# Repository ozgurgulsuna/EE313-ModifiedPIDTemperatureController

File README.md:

<h3 align="center" style=" border-bottom: none ;">EE313 Term Project </h3>
<p align="center">
   
<h2 align="center" style=" border-bottom: none ;">Design of an Autonomous Temperature Conditioning System Using Modified Analog PID Controller</h2>
<p align="center">

<h3 align="center" style=" border-bottom: none ;"> Project Summary </h3>
<p align="center">

<p align="justify">
&nbsp&nbsp Air conditioning can be described as the process of cooling, heating, moisturizing, dehumidifying, etc.
This method is utilized to create a more pleasant interior environment. In this project, you are required
to design an air conditioner system for small spaces. The system acquires heating, and cooling functions
and consists of one variable set input and four subsystems, namely, the control unit, display unit, sensing
unit, and the operation unit. The sensing unit provides the ambient temperature to the control unit, and
the temperature adjustment unit provides the desired temperature to the control unit. Figure 1 shows
the block diagram of the system.
</p>

<p align="center">
 </a>
</p>

<p align="justify">
&nbsp&nbsp Thus to design a responsive, fast, and accurate temperature control system PID method is a feasible choice. One challenge, of applying PID method to this problem is that the heating and cooling processes are not symmetric. To compensate that, a modified PID control circuit will be introduced in this paper. Also, to avoid the EMI (Electromagnetic Interference) and noise problems, the circuit is designed on a PCB (Printed Circuit Board). The heating element is a nickel-chromium wire and the cooling element is an 12V DC fan. The fan and the heater are driven with a MOSFET switch which is controlled by the generated PWM (Pulse Width Modulation) signals. The PWM for each switch is generated by comparing a triangular wave with the PID outputs.
</p>
   
<p align="justify">
&nbsp&nbsp The ambient temperature is measured using the LM35 analog temperature sensor. The set temperature value is adjusted with a potentiometer. The set and ambient temperatures are displayed by the display unit which consist of RGB LEDs (Red Green Blue Light Emitting Diodes), a constant current LED drive utilized by a transconductance amplifier. The display unit designed in a way to emit red light at 24°Cand below, green light at 32°Cand blue light at 40°C and above. The display output for the temperature intervals between those values are produced by combining the colors in a way that a smooth transition is observed while the set and ambient temperatures are changed.
</p>

<p align="justify">
&nbsp&nbsp In this project, first the design methodology and the mathematical analysis of each unit will be discussed in detail in section II. The circuit schematics and their analysis will be given in this part. The mechanical design and the manufacturing will be discussed in section III. Then, thermal modelling of the system will be explained in section IV. The results of the performed LTspice simulations will be given in section V. The experimental results and the comparison with the simulation will follow in section VI. Finally, the conclusions will be drawn in section VII.
</p>

<h3 align="center" style=" border-bottom: none ;"> Report </h3>
<p align="center">
   
<p align="justify">
&nbsp&nbsp In this <a href="https://github.com/ozgurgulsuna/EE313-ModifiedPIDTemperatureController/blob/main/Design%20of%20an%20Autonomous%20Temperature%20Conditioning%20System%20Using%20Modified%20PID%20Controller.pdf">report </a>, the design and implementation of an autonomous temperature conditioning system is demonstrated. Electrical and thermal systems are modelled in a single simulation environment with feedback loop closed. The PID method is shown that its applicable to this system, but due to the asymmetry of the reverse processes a modified PID circuit is proposed to damp oscillations of the system around the steady state, which is shown to be successful with the experimental results. Moreover, since the control signals are critical for the process, it is observed that filtering the noise with low and high pass filters and also avoiding the EMI effects with a careful PCB design procedure is essential for an accurate and reliable control mechanism.
</p>

<p align="center">
   </a>
</p>

<h3 align="center" style=" border-bottom: none ;"> Photographs </h3>

<p align="center">
   
<p align="center">
    
    &nbsp&nbsp 
    
</p>

<p align="center">
    
    &nbsp&nbsp 
    
</p>

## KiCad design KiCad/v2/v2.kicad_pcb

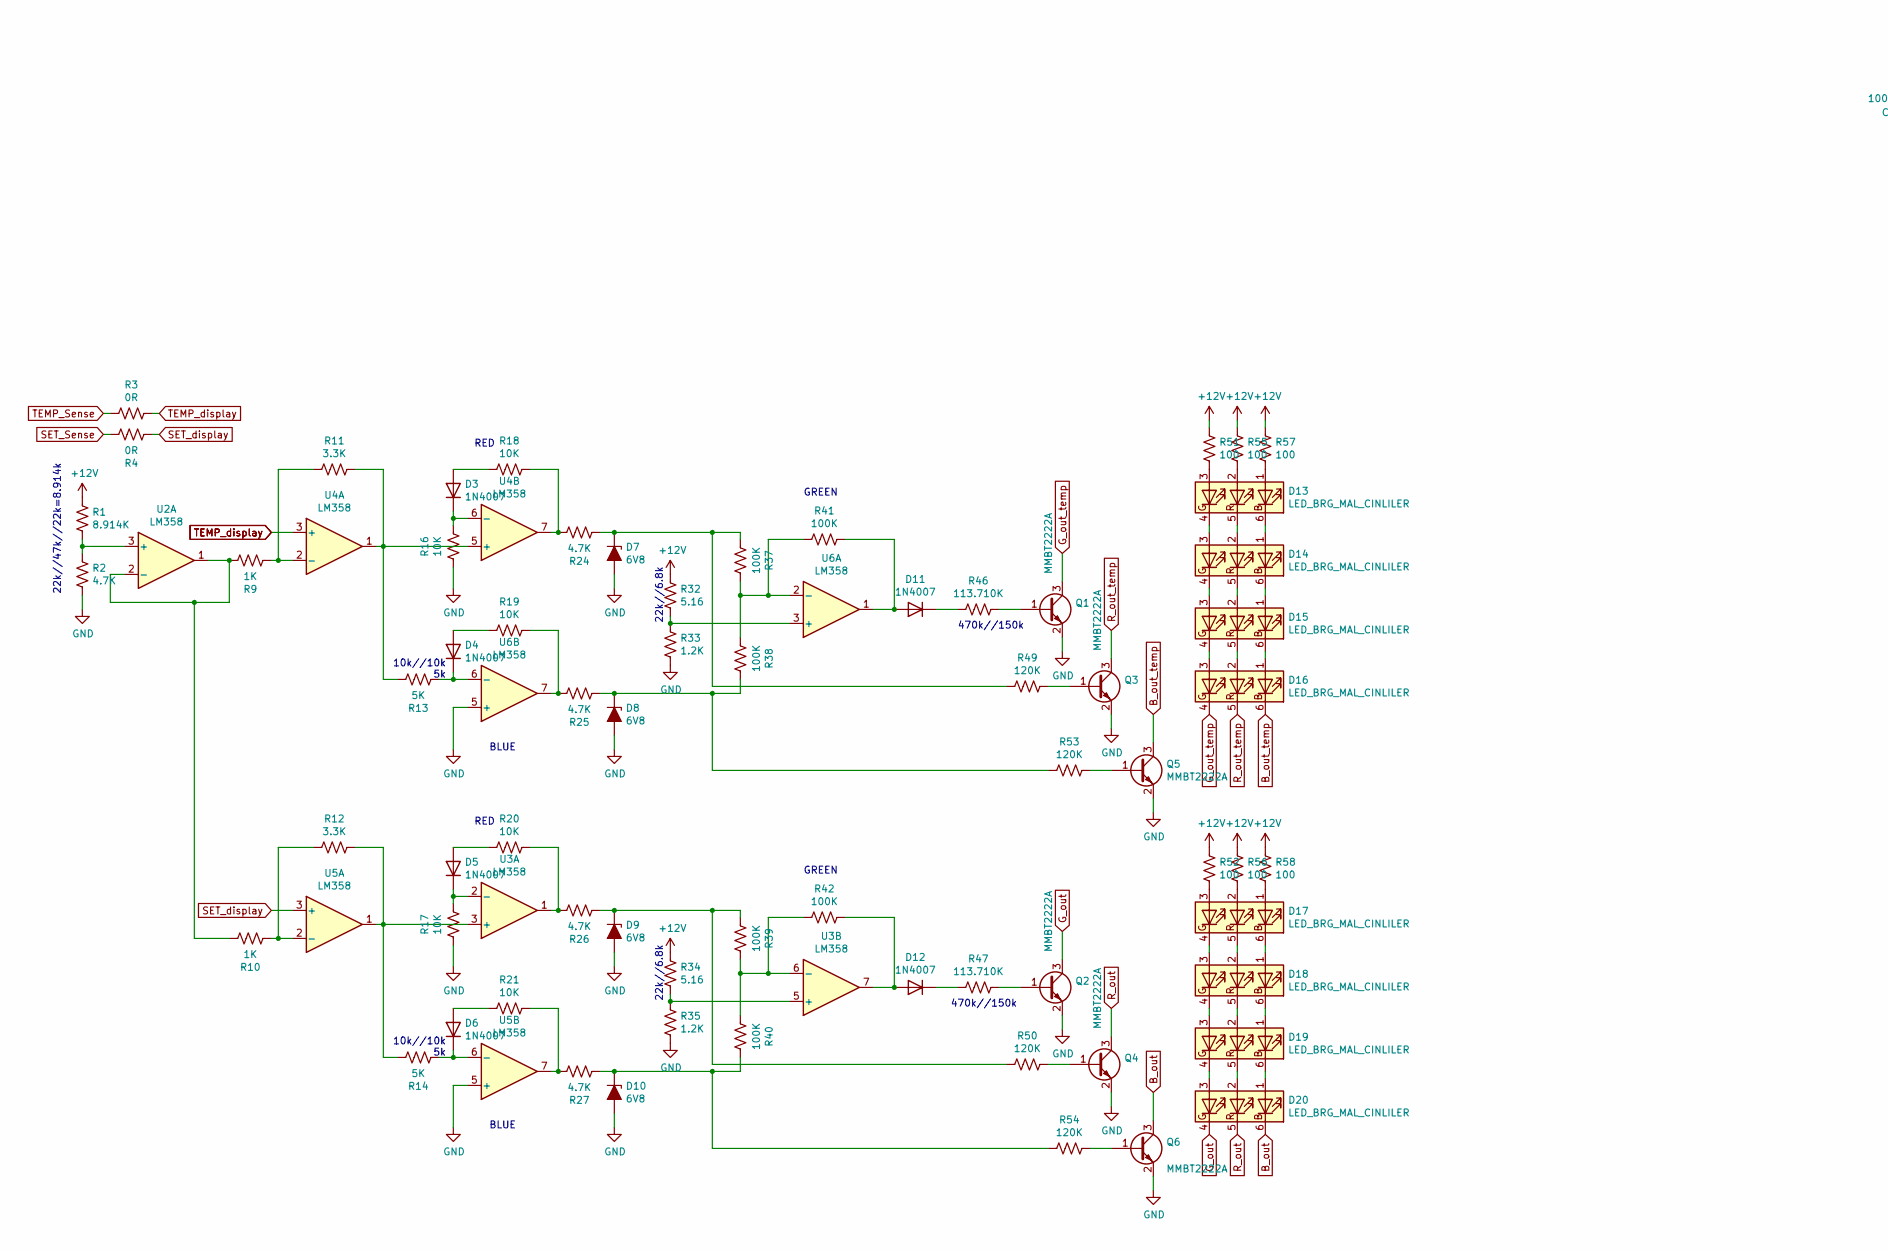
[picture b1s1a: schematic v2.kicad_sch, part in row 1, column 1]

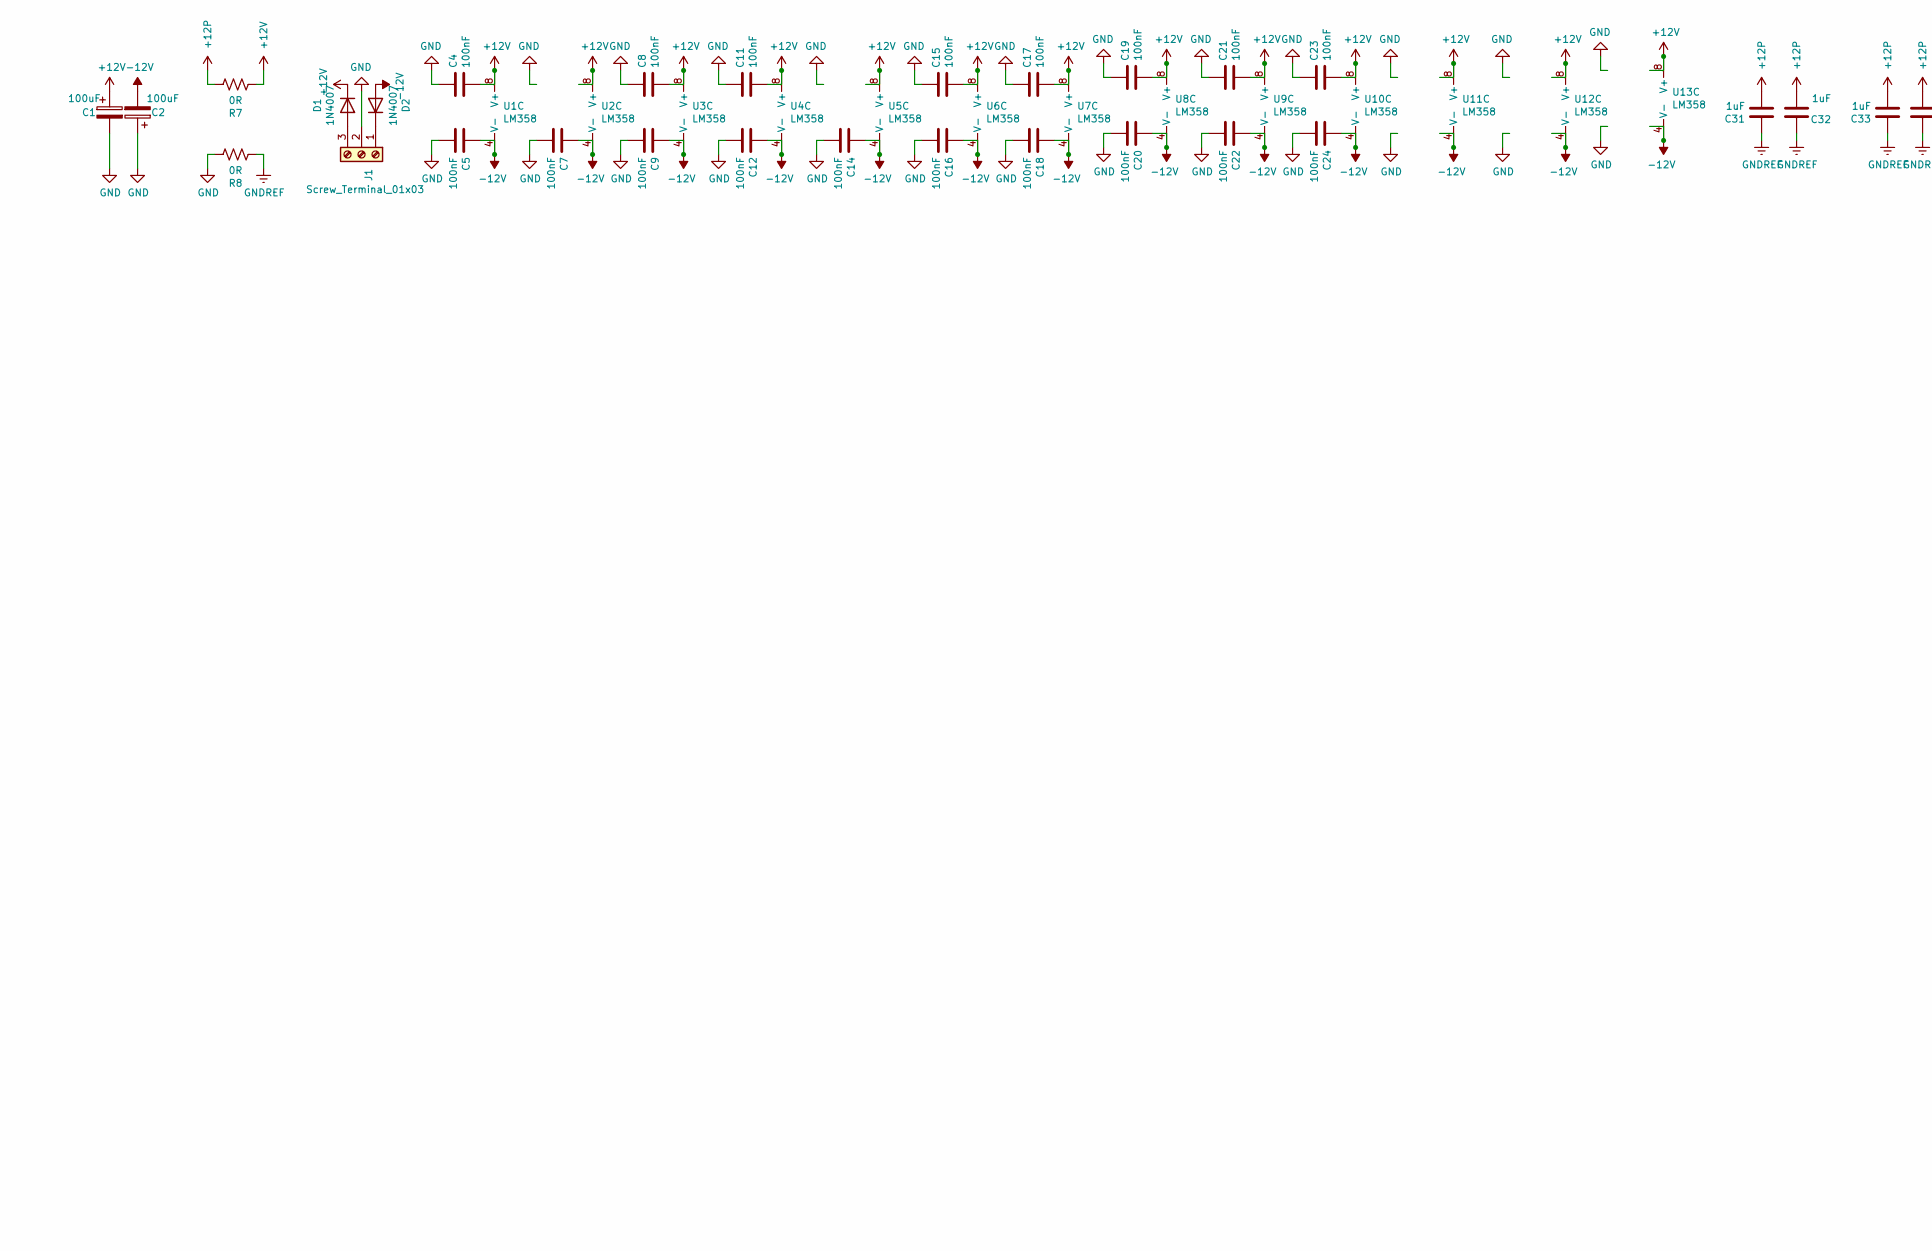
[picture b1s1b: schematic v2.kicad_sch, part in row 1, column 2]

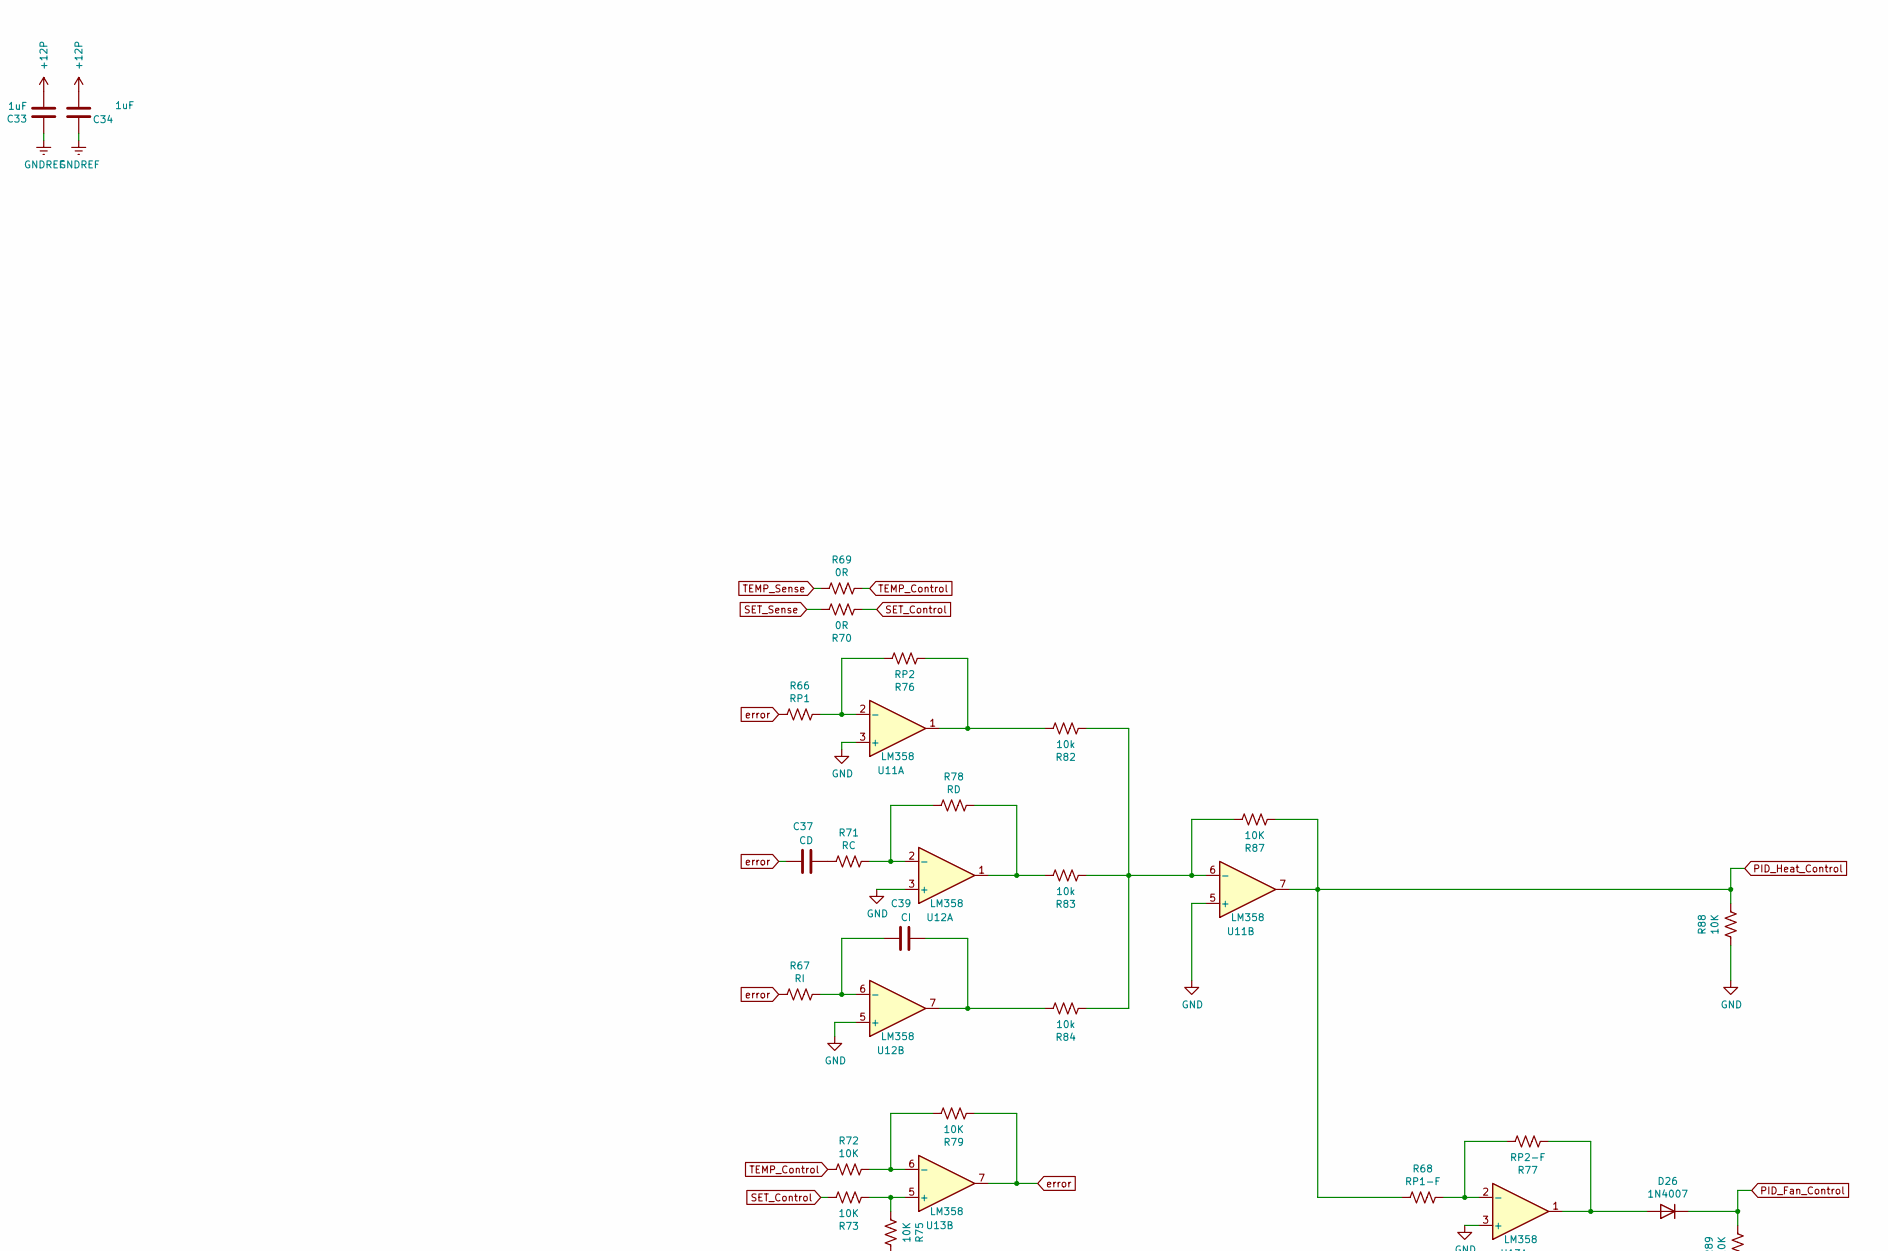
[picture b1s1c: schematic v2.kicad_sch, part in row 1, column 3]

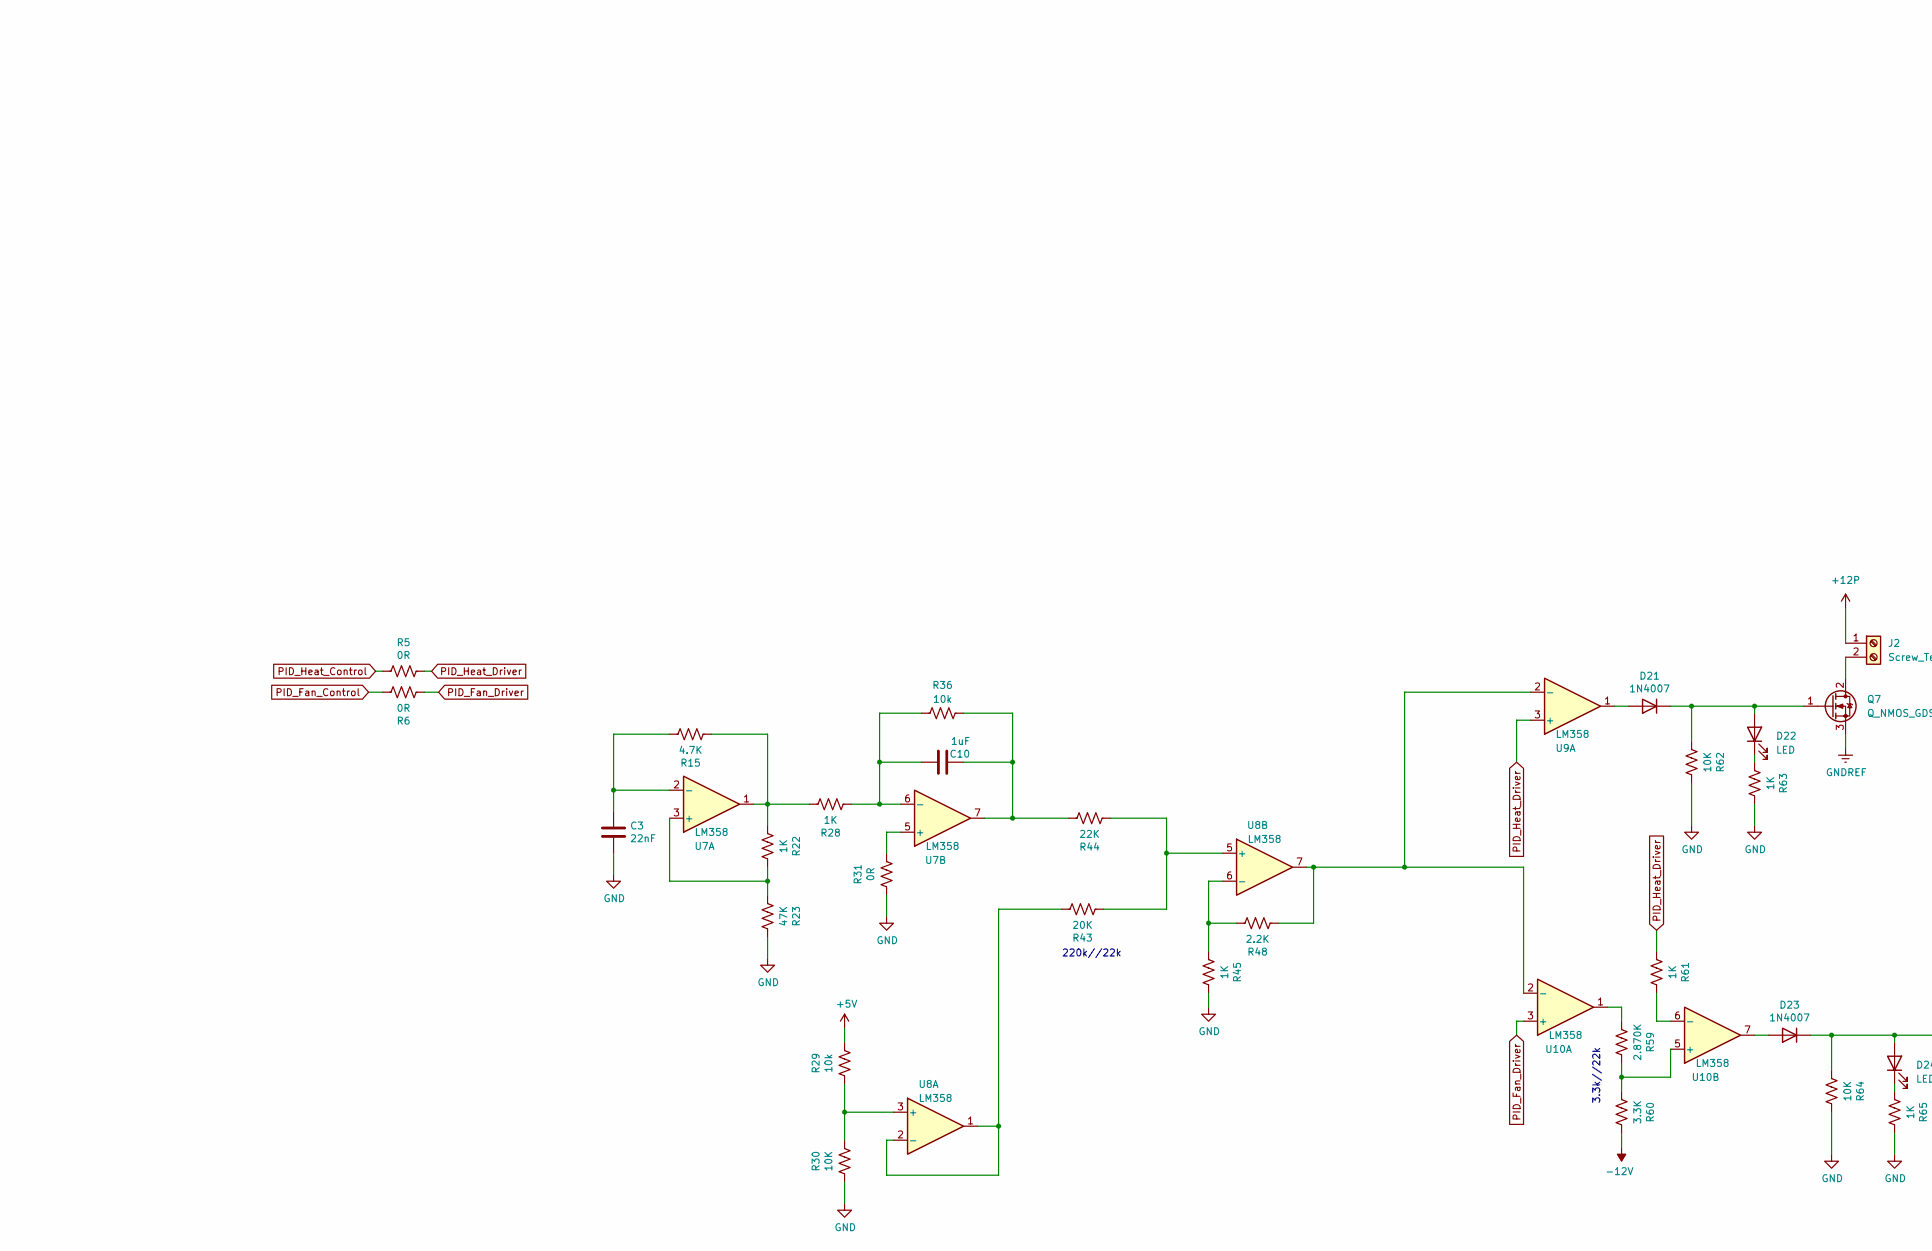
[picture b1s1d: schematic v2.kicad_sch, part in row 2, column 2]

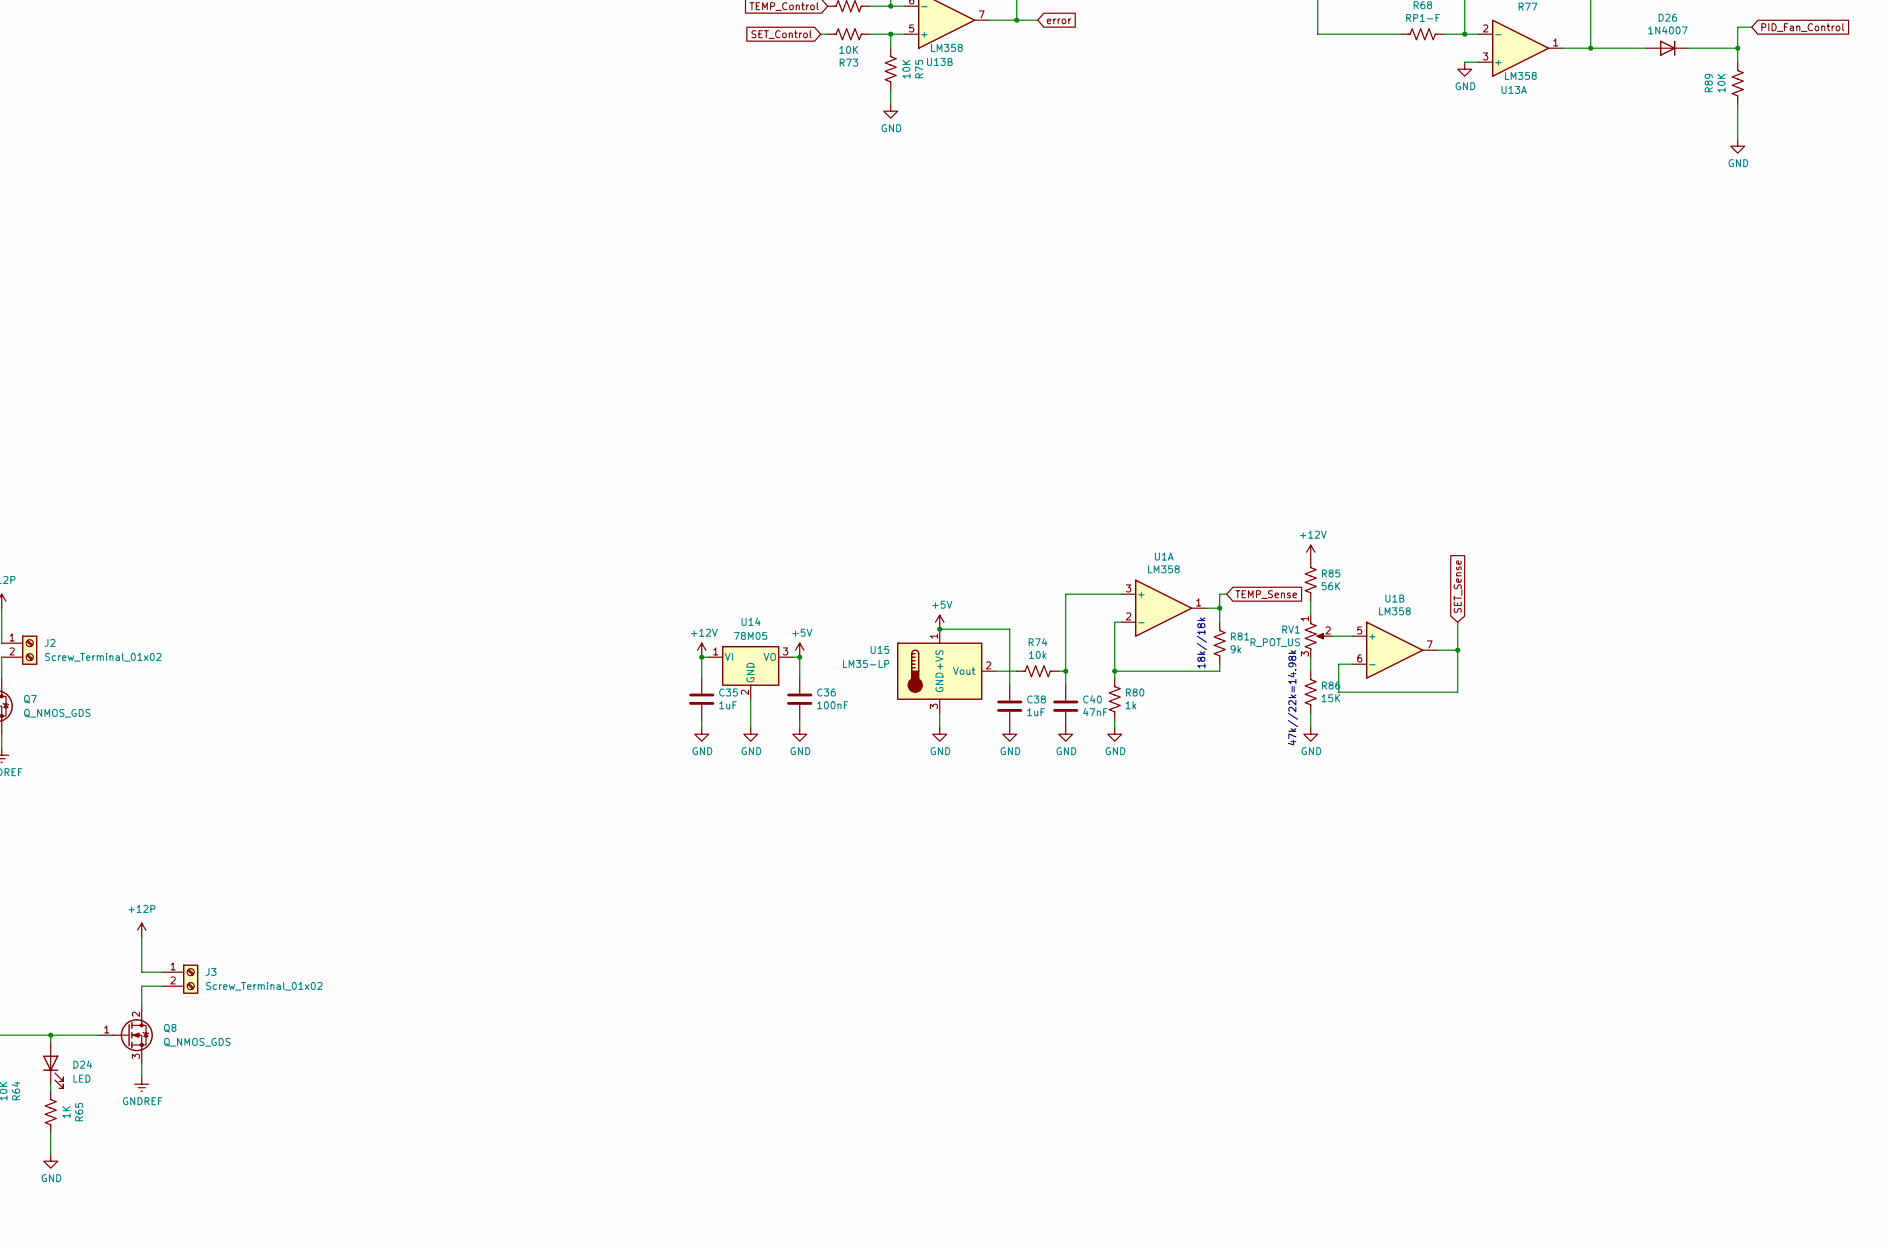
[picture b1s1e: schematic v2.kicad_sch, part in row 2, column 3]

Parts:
C1, C2: 100uF; CP_Elec_6.3x5.7
C3: 22nF; R_1206_3216Metric_Pad1.30x1.75mm_HandSolder
C4, C5, C7, C8, C9, C11, C12, C14, C15, C16, C17, C18, C19, C20, C21, C22, C23, C24, C36: 100nF; R_1206_3216Metric_Pad1.30x1.75mm_HandSolder
C10, C31, C32, C33, C34, C35, C38: 1uF; R_1206_3216Metric_Pad1.30x1.75mm_HandSolder
C37: CD; R_1206_3216Metric_Pad1.30x1.75mm_HandSolder
C39: CI; R_1206_3216Metric_Pad1.30x1.75mm_HandSolder
C40: 47nF; R_0805_2012Metric_Pad1.20x1.40mm_HandSolder
D1, D2, D3, D4, D5, D6, D11, D12, D21, D23, D26: 1N4007; D_SMA_Handsoldering
D7, D8, D9, D10: 6V8; D_A-405_P5.08mm_Vertical_KathodeUp
D13, D14, D15, D16, D17, D18, D19, D20: LED_BRG_MAL_CINLILER; LED_RGB_5050-6
D22, D24: LED; R_1206_3216Metric_Pad1.30x1.75mm_HandSolder
J1: Screw_Terminal_01x03; DEGSONx3x3.81mm
J2, J3: Screw_Terminal_01x02; R_Axial_DIN0204_L3.6mm_D1.6mm_P1.90mm_Vertical
Q1, Q2, Q3, Q4, Q5, Q6: MMBT2222A
Q7, Q8: Q_NMOS_GDS; TO-252-2
R1: 8.914K; R_1206_3216Metric_Pad1.30x1.75mm_HandSolder
R2, R15, R24, R25, R26, R27: 4.7K; R_1206_3216Metric_Pad1.30x1.75mm_HandSolder
R3, R4, R5, R6, R7, R8, R31, R69, R70: 0R; R_1206_3216Metric_Pad1.30x1.75mm_HandSolder
R9, R10, R22, R28, R45, R61, R63, R65: 1K; R_1206_3216Metric_Pad1.30x1.75mm_HandSolder
R11, R12, R60: 3.3K; R_1206_3216Metric_Pad1.30x1.75mm_HandSolder
R13, R14: 5K; R_1206_3216Metric_Pad1.30x1.75mm_HandSolder
R16, R17, R18, R19, R20, R21, R30, R62, R64, R72, R73, R75, R79, R87, R88, R89: 10K; R_1206_3216Metric_Pad1.30x1.75mm_HandSolder
R23: 47K; R_1206_3216Metric_Pad1.30x1.75mm_HandSolder
R29, R36, R74, R82, R83, R84: 10k; R_1206_3216Metric_Pad1.30x1.75mm_HandSolder
R32, R34: 5.16; R_1206_3216Metric_Pad1.30x1.75mm_HandSolder
R33, R35: 1.2K; R_1206_3216Metric_Pad1.30x1.75mm_HandSolder
R37, R38, R39, R40, R41, R42: 100K; R_1206_3216Metric_Pad1.30x1.75mm_HandSolder
R43: 20K; R_1206_3216Metric_Pad1.30x1.75mm_HandSolder
R44: 22K; R_1206_3216Metric_Pad1.30x1.75mm_HandSolder
R46, R47: 113.710K; R_1206_3216Metric_Pad1.30x1.75mm_HandSolder
R48: 2.2K; R_1206_3216Metric_Pad1.30x1.75mm_HandSolder
R49, R50, R53, R54: 120K; R_1206_3216Metric_Pad1.30x1.75mm_HandSolder
R51, R52, R55, R56, R57, R58: 100; R_1206_3216Metric_Pad1.30x1.75mm_HandSolder
R59: 2.870K; R_1206_3216Metric_Pad1.30x1.75mm_HandSolder
R66: RP1; R_1206_3216Metric_Pad1.30x1.75mm_HandSolder
R67: RI; R_1206_3216Metric_Pad1.30x1.75mm_HandSolder
R68: RP1-F; R_1206_3216Metric_Pad1.30x1.75mm_HandSolder
R71: RC; R_1206_3216Metric_Pad1.30x1.75mm_HandSolder
R76: RP2; R_1206_3216Metric_Pad1.30x1.75mm_HandSolder
R77: RP2-F; R_1206_3216Metric_Pad1.30x1.75mm_HandSolder
R78: RD; R_1206_3216Metric_Pad1.30x1.75mm_HandSolder
R80: 1k; R_1206_3216Metric_Pad1.30x1.75mm_HandSolder
R81: 9k; R_1206_3216Metric_Pad1.30x1.75mm_HandSolder
R85: 56K; R_1206_3216Metric_Pad1.30x1.75mm_HandSolder
R86: 15K; R_1206_3216Metric_Pad1.30x1.75mm_HandSolder
RV1: R_POT_US; 20kpot
U1, U2, U3, U4, U5, U6, U7, U8, U9, U10, U11, U12, U13: LM358; SOIC-8_3.9x4.9mm_P1.27mm
U14: 78M05; TO-252-2
U15: LM35-LP; TO-92

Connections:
+5V: C36.1, C38.1, R29.2, U14.3 (VO), U15.1 (+VS); also elsewhere on the board
+12P: C31.2, C32.2, C33.2, C34.2, J2.1, J3.1, R7.2
+12V: C1.1, C4.2, C8.2, C11.2, C15.2, C17.2, C19.2, C21.2, C23.2, C35.1, D1.1 (K), R1.2, R7.1, R32.2, R34.2, R51.1, R52.1, R55.1, R56.1, R57.1, R58.1, R85.2, U1.8 (V+), U2.8 (V+), U3.8 (V+), U4.8 (V+), U5.8 (V+), U6.8 (V+), U7.8 (V+), U8.8 (V+), U9.8 (V+), U10.8 (V+), U11.8 (V+), U12.8 (V+), U13.8 (V+), U14.1 (VI)
-12V: C2.2, C5.1, C7.1, C9.1, C12.1, C14.1, C16.1, C18.1, C20.1, C22.1, C24.1, D2.2 (A), R60.2, U1.4 (V-), U2.4 (V-), U3.4 (V-), U4.4 (V-), U5.4 (V-), U6.4 (V-), U7.4 (V-), U8.4 (V-), U9.4 (V-), U10.4 (V-), U11.4 (V-), U12.4 (V-), U13.4 (V-)
B_out: D20.6 (RA), Q6.3 (C)
B_out_temp: D16.6 (RA), Q5.3 (C)
G_out: D20.4 (BA), Q2.3 (C)
G_out_temp: D16.4 (BA), Q1.3 (C)
unnamed: C3.1, R15.2, U7.2 (-)
unnamed: C10.1, R28.1, R36.2, U7.6 (-)
unnamed: C10.2, R36.1, R44.2, U7.7
unnamed: C37.2, R71.1
unnamed: C39.1, R67.2, U12.6 (-)
unnamed: C39.2, R84.2, U12.7
unnamed: C40.1, R74.1, U1.3 (+)
unnamed: D1.2 (A), J1.3
unnamed: D2.1 (K), J1.1
unnamed: D3.1 (K), R16.2, U4.6 (-)
unnamed: D3.2 (A), R18.1
unnamed: D4.1 (K), R13.1, U6.6 (-)
unnamed: D4.2 (A), R19.1
unnamed: D5.1 (K), R17.2, U3.2 (-)
unnamed: D5.2 (A), R20.1
unnamed: D6.1 (K), R14.1, U5.6 (-)
unnamed: D6.2 (A), R21.1
unnamed: D7.1 (K), R24.1, R37.1, R49.1
unnamed: D8.1 (K), R25.1, R38.2, R53.1
unnamed: D9.1 (K), R26.1, R39.1, R50.1
unnamed: D10.1 (K), R27.1, R40.2, R54.1
unnamed: D11.1 (K), R46.1
unnamed: D11.2 (A), R41.2, U6.1
unnamed: D12.1 (K), R47.1
unnamed: D12.2 (A), R42.2, U3.7
unnamed: D13.1 (RK), R57.2
unnamed: D13.2 (GK), R55.2
unnamed: D13.3 (BK), R51.2
unnamed: D13.4 (BA), D14.3 (BK)
unnamed: D13.5 (GA), D14.2 (GK)
unnamed: D13.6 (RA), D14.1 (RK)
unnamed: D14.4 (BA), D15.3 (BK)
unnamed: D14.5 (GA), D15.2 (GK)
unnamed: D14.6 (RA), D15.1 (RK)
unnamed: D15.4 (BA), D16.3 (BK)
unnamed: D15.5 (GA), D16.2 (GK)
unnamed: D15.6 (RA), D16.1 (RK)
unnamed: D17.1 (RK), R58.2
unnamed: D17.2 (GK), R56.2
unnamed: D17.3 (BK), R52.2
unnamed: D17.4 (BA), D18.3 (BK)
unnamed: D17.5 (GA), D18.2 (GK)
unnamed: D17.6 (RA), D18.1 (RK)
unnamed: D18.4 (BA), D19.3 (BK)
unnamed: D18.5 (GA), D19.2 (GK)
unnamed: D18.6 (RA), D19.1 (RK)
unnamed: D19.4 (BA), D20.3 (BK)
unnamed: D19.5 (GA), D20.2 (GK)
unnamed: D19.6 (RA), D20.1 (RK)
unnamed: D21.1 (K), D22.2 (A), Q7.1 (G), R62.1
unnamed: D21.2 (A), U9.1
unnamed: D22.1 (K), R63.1
unnamed: D23.1 (K), D24.2 (A), Q8.1 (G), R64.1
unnamed: D23.2 (A), U10.7
unnamed: D24.1 (K), R65.1
unnamed: D26.2 (A), R77.1, U13.1
unnamed: J2.2, Q7.2 (D)
unnamed: J3.2, Q8.2 (D)
unnamed: Q1.1 (B), R46.2
unnamed: Q2.1 (B), R47.2
unnamed: Q3.1 (B), R49.2
unnamed: Q4.1 (B), R50.2
unnamed: Q5.1 (B), R53.2
unnamed: Q6.1 (B), R54.2
unnamed: R1.1, R2.2, U2.3 (+)
unnamed: R10.1, R12.1, U5.2 (-)
unnamed: R9.2, R10.2, U2.1, U2.2 (-)
unnamed: R9.1, R11.1, U4.2 (-)
unnamed: R11.2, R13.2, U4.1, U4.5 (+)
unnamed: R12.2, R14.2, U3.3 (+), U5.1
unnamed: R15.1, R22.1, R28.2, U7.1
unnamed: R18.2, R24.2, U4.7
unnamed: R19.2, R25.2, U6.7
unnamed: R20.2, R26.2, U3.1
unnamed: R21.2, R27.2, U5.7
unnamed: R22.2, R23.1, U7.3 (+)
unnamed: R29.1, R30.2, U8.3 (+)
unnamed: R31.2, U7.5 (+)
unnamed: R32.1, R33.2, U6.3 (+)
unnamed: R34.1, R35.2, U3.5 (+)
unnamed: R37.2, R38.1, R41.1, U6.2 (-)
unnamed: R39.2, R40.1, R42.1, U3.6 (-)
unnamed: R43.1, R44.1, U8.5 (+)
unnamed: R43.2, U8.1, U8.2 (-)
unnamed: R45.1, R48.2, U8.6 (-)
unnamed: R48.1, U8.7, U9.2 (-), U10.2 (-)
unnamed: R59.1, U10.1
unnamed: R59.2, R60.1, U10.5 (+)
unnamed: R61.2, U10.6 (-)
unnamed: R66.2, R76.2, U11.2 (-)
unnamed: R68.2, R77.2, U13.2 (-)
unnamed: R71.2, R78.1, U12.2 (-)
unnamed: R72.2, R79.2, U13.6 (-)
unnamed: R73.1, R75.1, U13.5 (+)
unnamed 102: R74.2, U15.2 (Vout); also elsewhere on the board
unnamed: R76.1, R82.2, U11.1
unnamed: R78.2, R83.2, U12.1
unnamed: R80.2, R81.1, U1.2 (-)
unnamed: R82.1, R83.1, R84.1, R87.2, U11.6 (-)
unnamed: R85.1, RV1.1
unnamed: R86.2, RV1.3
unnamed: RV1.2, U1.5 (+)
PID_Fan_Control: D26.1 (K), R6.2, R89.2
PID_Fan_Driver: R6.1, U10.3 (+)
PID_Heat_Driver: R5.2, R61.1, U9.3 (+)
R_out: D20.5 (GA), Q4.3 (C)
R_out_temp: D16.5 (GA), Q3.3 (C)
SET_Control: R70.1, R73.2
SET_Sense: R4.2, R70.2, U1.6 (-), U1.7
SET_display: R4.1, U5.3 (+)
TEMP_Control: R69.2, R72.1
TEMP_Sense: R3.1, R69.1, R81.2, U1.1
TEMP_display: R3.2, U4.3 (+)

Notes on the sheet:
220k//22k
GREEN
22k//47k//22k=8.914k
RED
10k//10k 5k
470k//150k
22k//6.8k
47k//22k=14.98k
3.3k//22k
BLUE
18k//18k

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
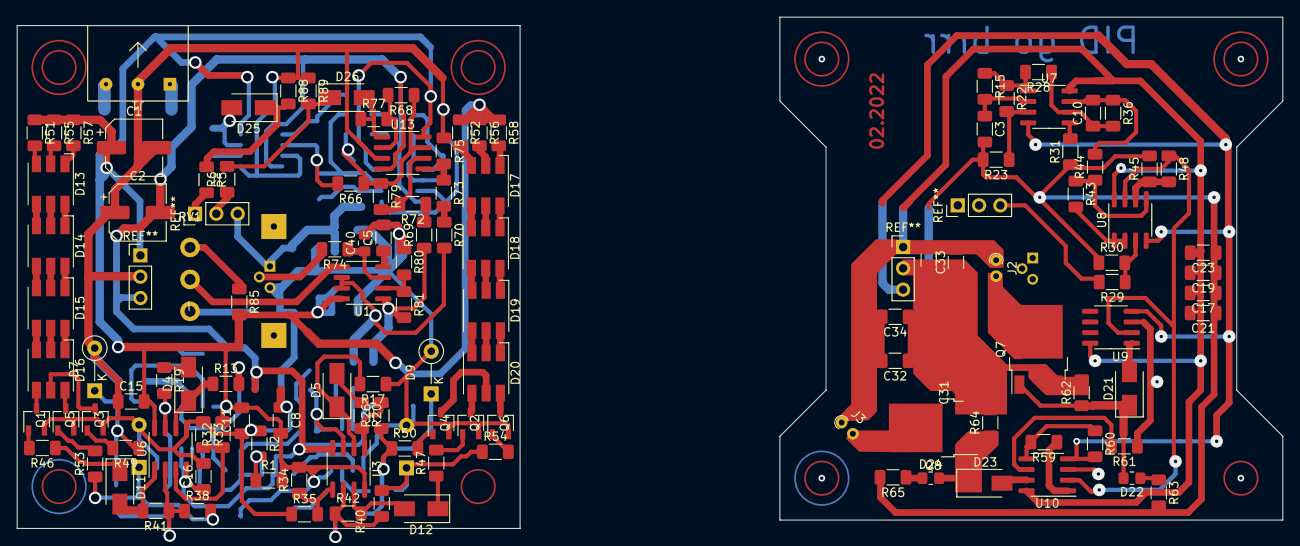
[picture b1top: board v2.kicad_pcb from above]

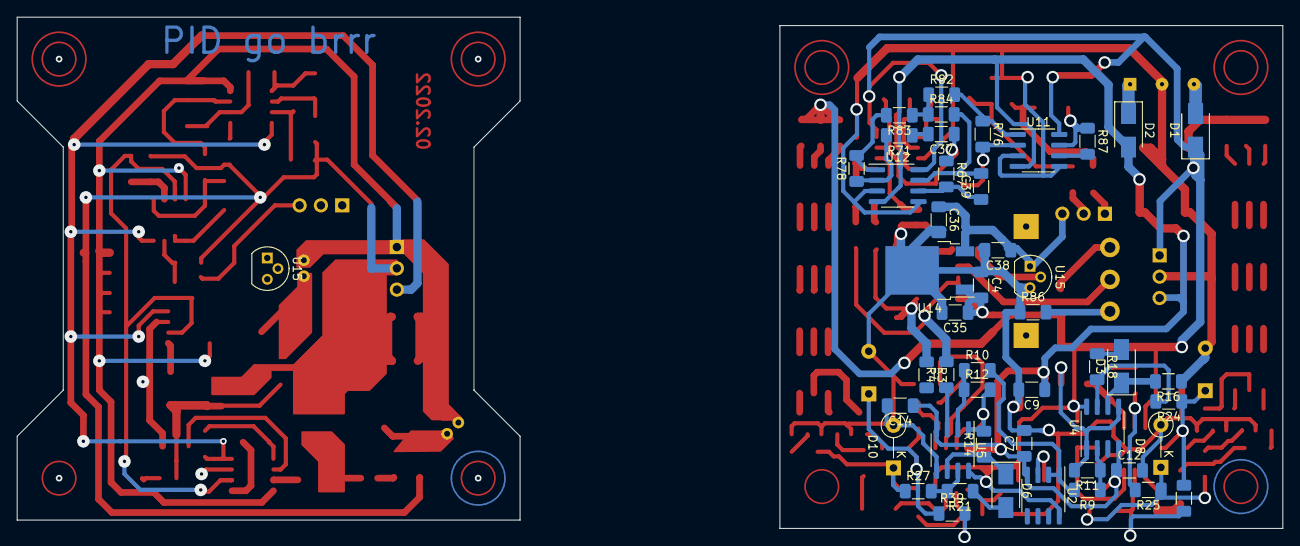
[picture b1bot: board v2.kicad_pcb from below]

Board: 4 copper layers, 151.0 x 61.0 mm, 169 parts (48 on the bottom side), 126 nets.

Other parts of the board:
D25: 1N4007; D_SMA
U15#2: LM35-LP; TO-92

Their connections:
+5V: U15#2.1 (+VS); also elsewhere on the board
unnamed 102: U15#2.2 (Vout); also elsewhere on the board

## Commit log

2022-01-07 Project desciption
2022-01-16 first report phase has passed
2022-03-05 Add files via upload
    pcb exports from kicad
2022-03-05 Add files via upload
    results
2022-03-05 Add files via upload
    tex for the final report
2022-03-05 Add files via upload
    final report and reference links
2022-03-05 Add files via upload
    readme previews are added
2022-03-05 Add files via upload
    all the asc files
2022-03-05 Add files via upload
    pcb projects are added
2022-03-05 Add files via upload
    pcb outputs in pdf format
2022-07-26 [Reallocation] organizing the folders
2022-07-26 [Readme] Images uploaded
2022-07-26 [Readme] Update on summary
2022-08-02 [ReadMe] new test images
2022-08-02 [ReadMe] Update on pictures
